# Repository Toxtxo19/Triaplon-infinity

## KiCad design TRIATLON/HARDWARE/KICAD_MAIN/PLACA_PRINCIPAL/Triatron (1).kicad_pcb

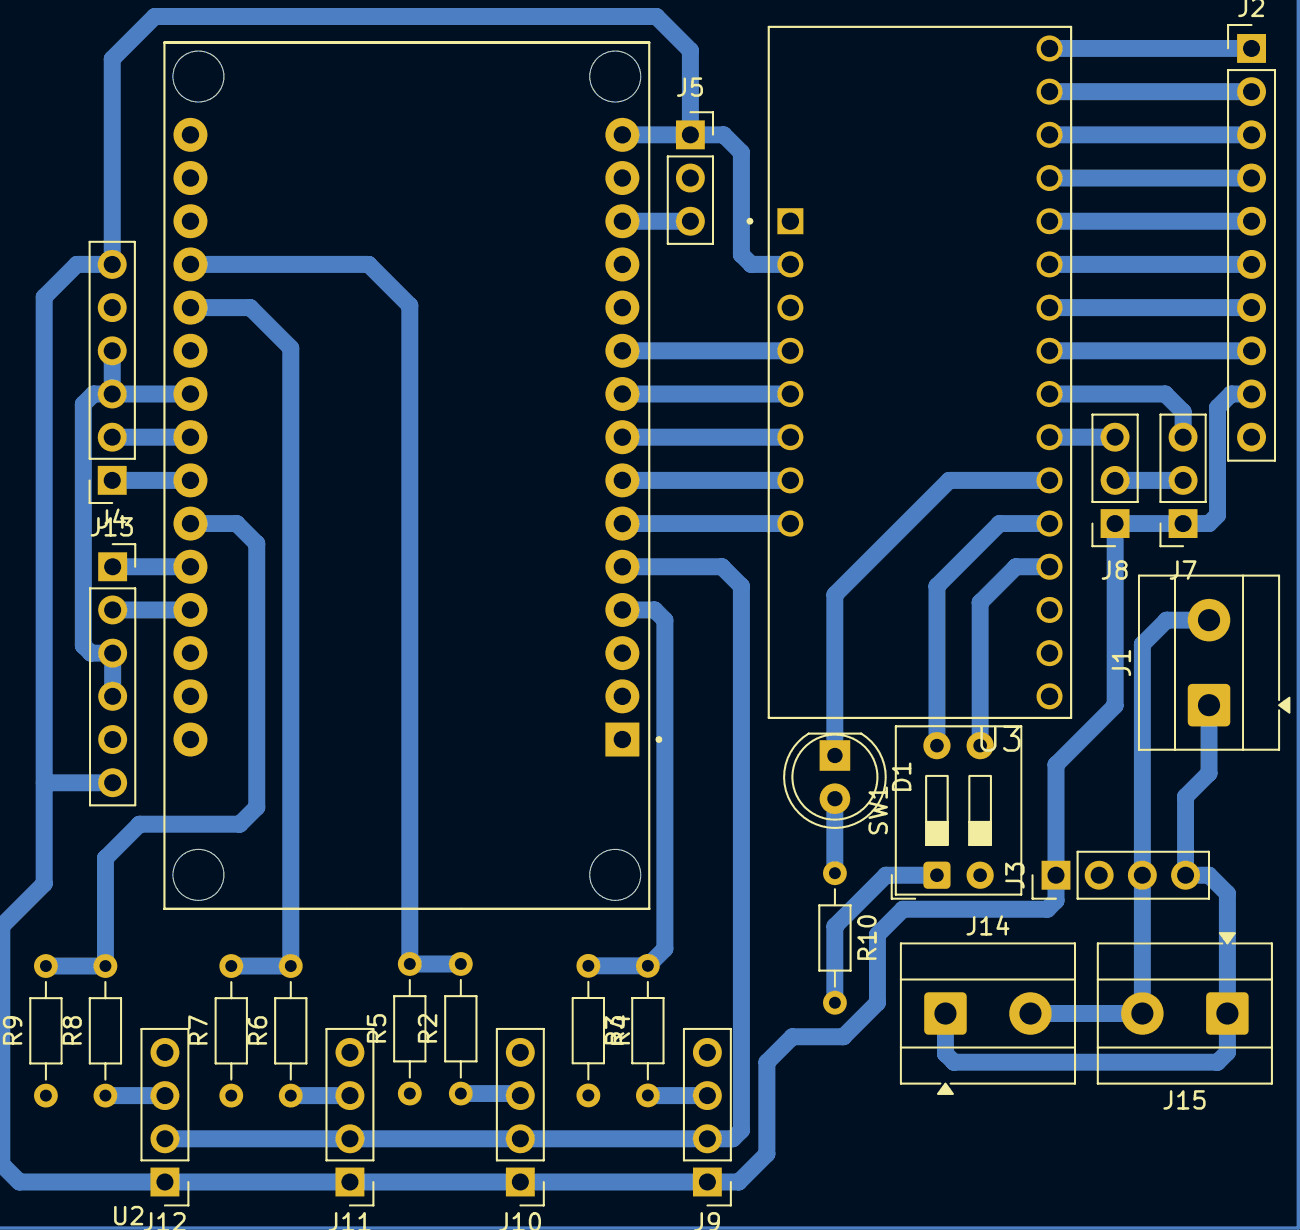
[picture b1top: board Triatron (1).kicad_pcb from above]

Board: 2 copper layers, 27 parts (0 on the bottom side), 38 nets.

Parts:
D1: LED; LED_D5.0mm
J1, J14, J15: Screw_Terminal_01x02; TerminalBlock_MetzConnect_Type055_RT01502HDWU_1x02_P5.00mm_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
J2: Conn_01x10_Pin; PinHeader_1x10_P2.54mm_Vertical
J3: Conn_01x04_Pin; PinHeader_1x04_P2.54mm_Vertical
J4, J13: Conn_01x06_Pin; PinSocket_1x06_P2.54mm_Vertical
J5: infrarrojo; PinSocket_1x03_P2.54mm_Vertical
J7, J8: Conn_01x03_Pin; PinSocket_1x03_P2.54mm_Vertical
J9, J10, J11, J12: HC-04; PinHeader_1x04_P2.54mm_Vertical
R2, R5, R6, R7, R8, R9: R; R_Axial_DIN0204_L3.6mm_D1.6mm_P7.62mm_Horizontal
R3: 1k; R_Axial_DIN0204_L3.6mm_D1.6mm_P7.62mm_Horizontal
R4: 2k; R_Axial_DIN0204_L3.6mm_D1.6mm_P7.62mm_Horizontal
R10: 220; R_Axial_DIN0204_L3.6mm_D1.6mm_P7.62mm_Horizontal
SW1: SW_DIP_x02; SW_DIP_SPSTx02_Slide_9.78x7.26mm_W7.62mm_P2.54mm
U2: ESP32_30PIN; MODULE_ESP32_DEVKIT_V1
U3: BOB-09056; MODULE_BOB-09056

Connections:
A2: J5.3, U2.13 (GPIO13)
D0: J7.3, U3.JP1-9 (C8)
D1: J2.1, U3.JP1-1 (C0)
D2: J2.2, U3.JP1-2 (C1)
D3: J2.3, U3.JP1-3 (C2)
D4: J2.4, U3.JP1-4 (C3)
D5: J2.5, U3.JP1-5 (C4)
D6: J2.6, U3.JP1-6 (C5)
D7: J2.7, U3.JP1-7 (C6)
D8: J2.8, U3.JP1-8 (C7)
D9: J8.3, U3.JP1-10 (C9)
D10: D1.1 (K), U3.JP1-11 (C10)
ECHO1: R3.2, R4.1, U2.4 (GPIO34)
ECHO2: R2.2, R5.2, U2.19 (GPIO2)
ECHO3: R6.2, R7.2, U2.20 (GPIO4)
ECHO4: R8.2, R9.2, U2.25 (GPIO19)
EN: J4.3, J4.4, J13.3, J13.4, U2.22 (GPIO17)
GND: J1.2, J3.3, J14.2, J15.2
unnamed: D1.2 (A), R10.1
unnamed: J9.3, R3.1
unnamed: J10.3, R2.1
unnamed: J11.3, R6.1
unnamed: J12.3, R8.1
OUT+: J2.9, J3.1, J4.6, J5.1, J7.1, J8.1, J9.1, J10.1, J11.1, J12.1, J13.6, U2.15 (VIN), U3.JP3-2 (VCC)
OUT-: J2.10, J3.2, J4.5, J5.2, J7.2, J8.2, J9.4, J10.4, J11.4, J12.4, J13.5, R4.2, R5.1, R7.1, R9.1, R10.2, SW1.1, SW1.2, U2.14 (GND), U3.JP3-1 (GND)
PWM-L: J4.1, U2.26 (GPIO21)
PWM-L 2: J13.1, U2.24 (GPIO18)
PWM-R: J4.2, U2.27 (GPIO3)
PWM-R 2: J13.2, U2.23 (GPIO5)
S0: U2.10 (GPIO27), U3.JP3-4 (S0)
S1: U2.9 (GPIO26), U3.JP3-5 (S1)
S2: U2.8 (GPIO25), U3.JP3-6 (S2)
S3: U2.7 (GPIO33), U3.JP3-7 (S3)
SIG: U2.6 (GPIO32), U3.JP3-8 (COM)
SW1: SW1.3, U3.JP1-13 (C12)
SW2: SW1.4, U3.JP1-12 (C11)
TRIG1: J9.2, J10.2, J11.2, J12.2, U2.5 (GPIO35)
VCC: J1.1, J3.4, J14.1, J15.1

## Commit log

2025-06-03 actualice
2025-06-17 actualizado
